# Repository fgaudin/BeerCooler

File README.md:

BeerCooler
==========

Arduino app to cool beer with fans

Usage
-----
Displaying 0 to 9 means 60 to 69F, 0. to 9. means 70 to 79F
Press high button to switch to high limit setting. Press low button to switch to low limit setting.
If low limit < high limit, fans turn on when temperature > high limit and turn off when temperature < low limit
If low limit > high limit, fans turn on when temperature < high limit and turn off when temperature > low limit

Components
-------------------

Some of the components used:

 - DS18B20 https://www.sparkfun.com/products/11050
 - 2 12V 120mm PC fans
 - 2 transistors NPN 2N3904 https://www.sparkfun.com/products/521
 - optoisolator https://www.sparkfun.com/products/314

Libraries
---------

 - https://github.com/fgaudin/Led7Seg
 - https://github.com/fgaudin/PushButton

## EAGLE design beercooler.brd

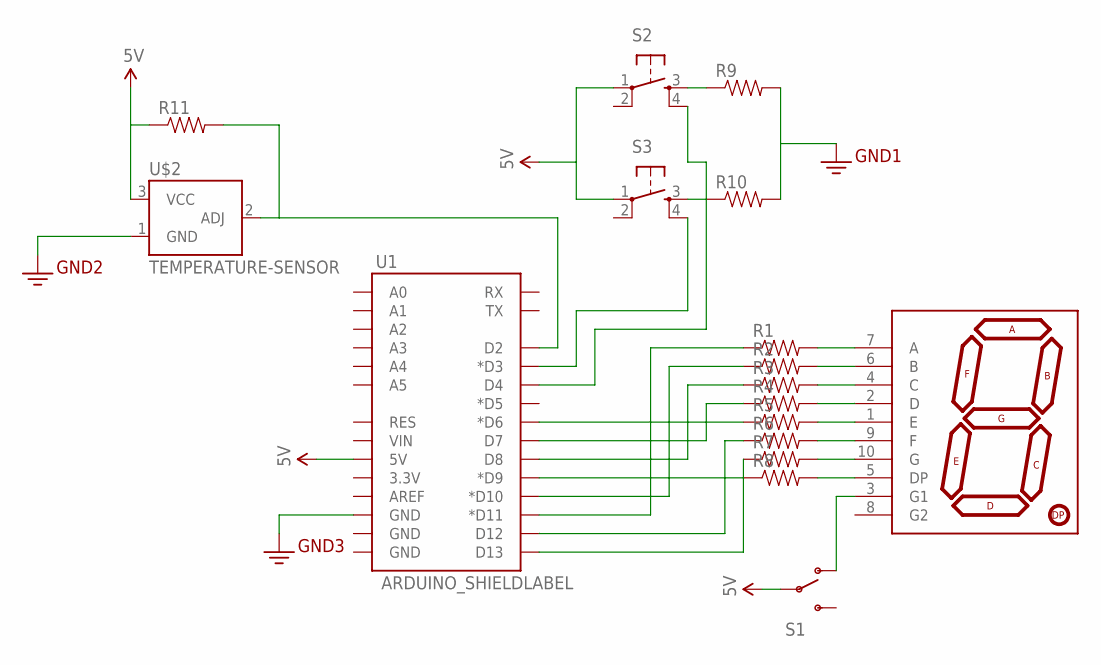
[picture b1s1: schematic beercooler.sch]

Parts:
R1, R2, R3, R4, R5, R6, R7, R8, R9, R10, R11: RESISTORPTH-1/4W; AXIAL-0.4
S1: SWITCH-SPDT-SMD-A; SWITCH-SPST-SMD-A
S2, S3: TAC_SWITCHPTH; TACTILE-PTH
U1: ARDUINO_SHIELDLABEL; DUEMILANOVE_SHIELD
U$1: 7-SEGMENT-DISPLAY-1"-RED; 7-SEGMENT-1"PTH
U$2: TEMPERATURE-SENSOR; TO-92

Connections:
3.3V: U1.GND@2 (GND), U$2.1 (GND)
5V: R11.P$1 (1), S1.2, S2.1, S3.1, U1.5V, U$2.3 (VCC)
unnamed: R1.P$2 (2), U$1.7 (A)
unnamed: R2.P$2 (2), U$1.6 (B)
unnamed: R3.P$2 (2), U$1.4 (C)
unnamed: R4.P$2 (2), U$1.2 (D)
unnamed: R5.P$2 (2), U$1.1 (E)
unnamed: R6.P$2 (2), U$1.9 (F)
unnamed: R7.P$2 (2), U$1.10 (G)
unnamed: R8.P$2 (2), U$1.5 (DP)
unnamed: R5.P$1 (1), U1.D6 (*D6)
unnamed: R4.P$1 (1), U1.D7
unnamed: R3.P$1 (1), U1.D8
unnamed: R8.P$1 (1), U1.D9 (*D9)
unnamed: R2.P$1 (1), U1.D10 (*D10)
unnamed: R1.P$1 (1), U1.D11 (*D11)
unnamed: R6.P$1 (1), U1.D12
unnamed: R7.P$1 (1), U1.D13
unnamed: R10.P$1 (1), S3.3
unnamed: R9.P$1 (1), S2.3
unnamed: R9.P$2 (2), R10.P$2 (2)
unnamed: S3.4, U1.D3 (*D3)
unnamed: S2.4, U1.D4
unnamed: S1.1 (O), U$1.3 (G1)
unnamed: R11.P$2 (2), U1.D2, U$2.2 (ADJ)

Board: 2 copper layers, 17 parts (0 on the bottom side), 25 nets, no tracks yet.

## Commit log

2013-05-28 Initial import
2013-06-02 Eagle files
2013-06-04 Updated eagle schema
2013-06-04 Added a missing resistor
2013-06-09 Changed pins following soldering and fixed schematic
2013-06-12 Removed a switch
2013-06-14 If high limit < low limit, act as a beer warmer
2013-06-14 Do not write to the eeprom on each boot

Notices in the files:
parts and their libraries:
SparkFun-Resistors: Licensing: CC v3.0 Share-Alike You are welcome to use this library for commercial purposes.
